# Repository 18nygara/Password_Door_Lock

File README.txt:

Password based door locking mechanism - 12 key allows user to input a password which will be reflected on the screen provided on the unit. USB interface allows 
one to set a password and change settings in the device, software is not included in the repo.

WARNING! ~~~ IF TRYING TO COPY THIS REPO, IT WILL NOT WORK ON YOUR LOCAL MACHINE ~~~

Because of the absolute pathing on KiCAD file libraries, downloading this project will NOT allow one to modify the design.
All footprint, 3D, and library modules were provided via UltraLibrarian, SnapEDA, DigiKey, or were custom designed - they can be resourced but not copied directly from here.

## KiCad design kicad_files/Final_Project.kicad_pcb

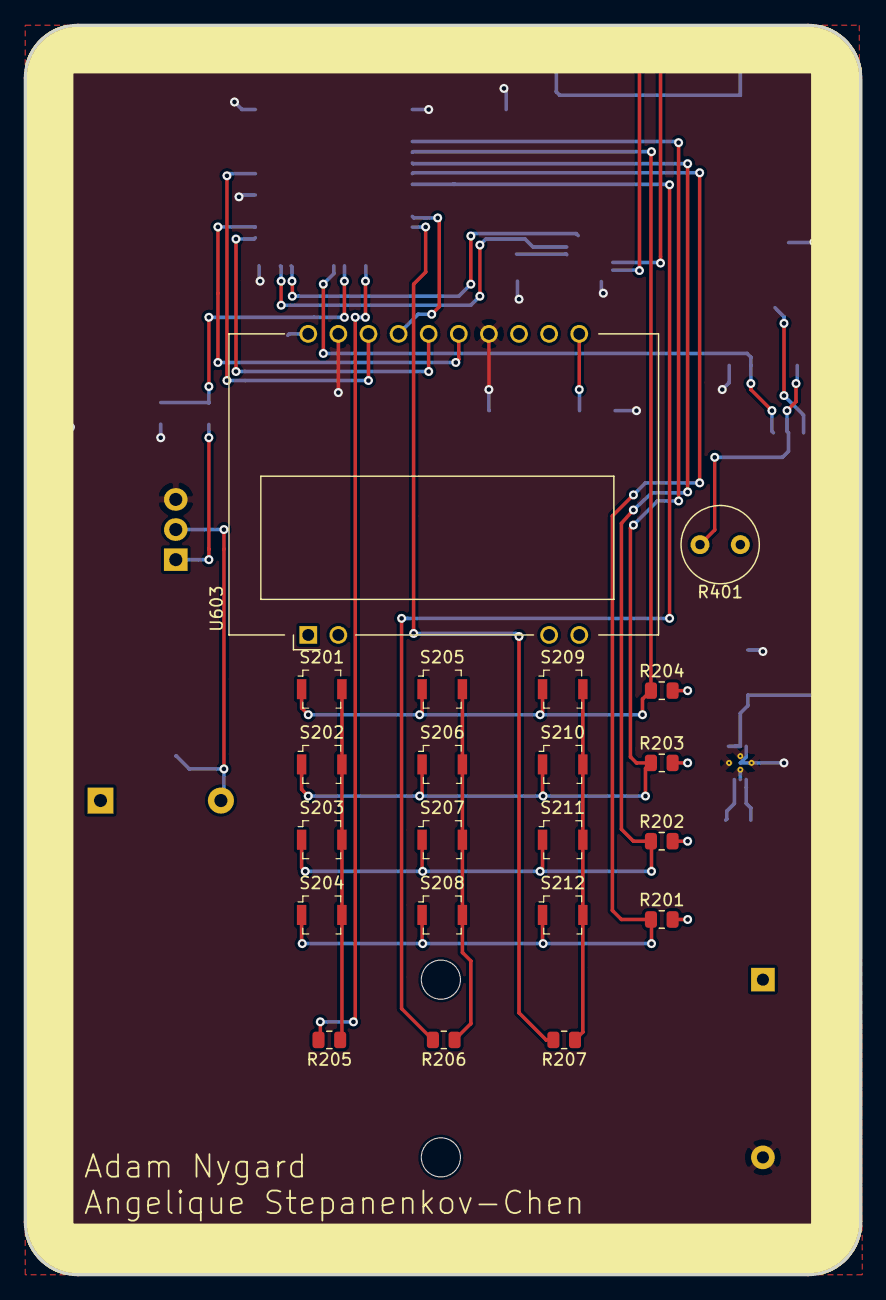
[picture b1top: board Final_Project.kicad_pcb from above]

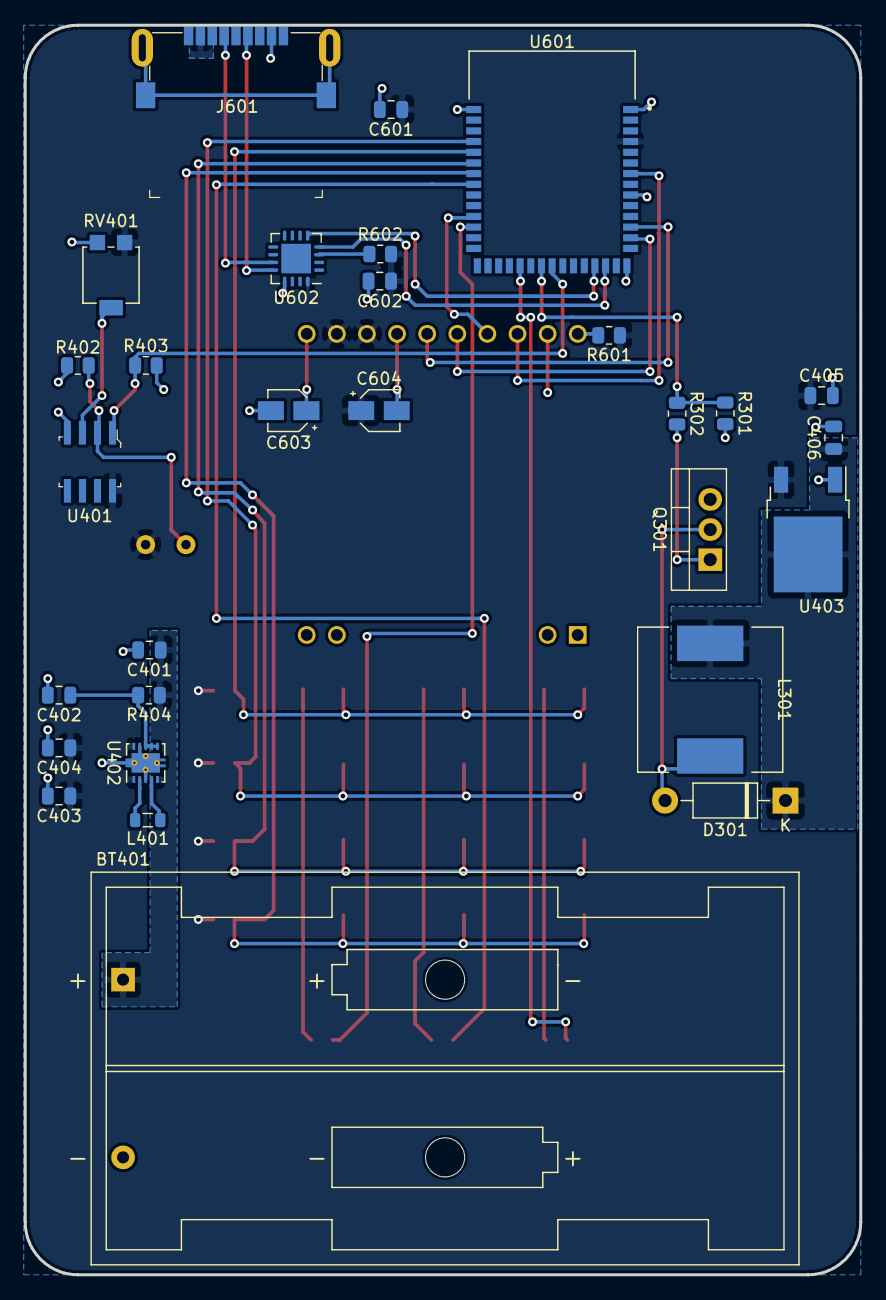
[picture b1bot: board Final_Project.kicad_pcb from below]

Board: 2 copper layers, 70.5 x 105.4 mm, 50 parts (29 on the bottom side), 34 nets.

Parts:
BT401: 3V; BatteryHolder_Keystone_2462_2xAA
C401, C403, C404, C405, C406, C601, C602: 10uF; C_0805_2012Metric
C402: 0.1uF; C_0805_2012Metric
C603, C604: 1uF; CP_Elec_3x5.3
D301: 1N4007; D_DO-41_SOD81_P10.16mm_Horizontal
J601: AU-Y1006-3; USB_A_Female_AU-Y1006-3
L301: 322mH; L_Pulse_PA4320
L401: 2.2uH; L_0805_2012Metric
Q301: IRF540N; TO-220-3_Vertical
R201, R202, R203, R204, R301, R302, R402: 10K; R_0805_2012Metric
R205, R206, R207, R403: 470; R_0805_2012Metric
R401: A1050; R_LDR_D6.4mm_P3.4mm_Vertical
R404: 100; R_0805_2012Metric
R601, R602: 10k; R_0805_2012Metric
RV401: 20K; Potentiometer_Bourns_3314G_Vertical
S201, S202, S203, S204, S205, S206, S207, S208, S209, S210, S211, S212: B3U-1000P; Switch_Tactile_SMD_B3U-1000P
U401: LM358DR; SOIC-8_W3.9mm
U402: TPS63001; Texas_DRC0010J_ThermalVias
U403: NCP1117-12_TO252; TO-252-2
U601: CYBLE-416045-02; XCVR_CYBLE-416045-02
U602: MCP2221AxML; QFN-16-1EP_4x4mm_P0.65mm_EP2.5x2.5mm
U603: EA_DOGS104B-A; EA_DOGS104X-A

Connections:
+3V3: C403.1, C404.1, C405.1, C601.1, C602.1, C604.1, R201.2, R202.2, R203.2, R204.2, R401.1, R601.1, R602.2, RV401.1, U401.8, U402.1, U402.10, U403.3, U601.4, U602.16, U603.12, U603.13
+12V: C406.1, D301.1, L301.1, U403.2
/Keypad/KYPD_CL_0: R205.2, U601.25
/Keypad/KYPD_CL_1: R206.2, U601.36
/Keypad/KYPD_CL_2: R207.2, U601.32
/Keypad/KYPD_COL_CNCT0: R205.1, S201.2, S202.2, S203.2, S204.2
/Keypad/KYPD_COL_CNCT1: R206.1, S205.2, S206.2, S207.2, S208.2
/Keypad/KYPD_COL_CNCT2: R207.1, S209.2, S210.2, S211.2, S212.2
/Keypad/KYPD_RW_0: R204.1, S201.1, S205.1, S209.1, U601.39
/Keypad/KYPD_RW_1: R203.1, S202.1, S206.1, S210.1, U601.40
/Keypad/KYPD_RW_2: R202.1, S203.1, S207.1, S211.1, U601.38
/Keypad/KYPD_RW_3: R201.1, S204.1, S208.1, S212.1, U601.37
/Light_Sensor/LIGHT_DIV: R401.2, R402.1, U401.2
/Light_Sensor/LIGHT_OUT: R403.1, U401.1, U601.22
/Light_Sensor/V_THRESH: RV401.2, U401.3
/Lock_Mechanism/MOS_GATE: Q301.1, R302.2
/Lock_Mechanism/MTR_CTRL: D301.2, L301.2, Q301.2
/Lock_Mechanism/MTR_ON: R301.1, R302.1, U601.23
/MCU/D+: J601.3, U602.12
/MCU/D-: J601.2, U602.11
/MCU/RST_N_SCR: R601.2, U603.20
/MCU/RST_N_USB: R602.1, U602.3
/MCU/V_OUT_SCR: C603.1, U603.11
/Power_Supply/EN: C402.1, R404.2, U402.6, U402.7, U402.8
/Power_Supply/INDCTR_LFT: L401.1, U402.4
/Power_Supply/INDCTR_RGHT: L401.2, U402.2
/Power_Supply/VBAT_IN: BT401.1, C401.1, R404.1, U402.5
GND: BT401.2, C401.2, C402.2, C403.2, C404.2, C405.2, C406.2, C601.2, C602.2, C603.2, C604.2, J601.4, Q301.3, R301.2, R402.2, R403.2, RV401.3, U401.4, U402.3, U402.9, U402.11, U403.1, U601.1, U601.9, U601.15, U601.43, U602.13, U603.14, U603.19
MISO: U601.12, U603.15
MOSI: U601.13, U603.16
SCLK: U601.33, U603.17
SS_0: U601.7, U603.18
USB_UART_RX: U601.17, U602.4
USB_UART_TX: U601.18, U602.5

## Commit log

2021-04-30 Add initial KiCAD files
2021-04-30 Add PCB and 3D rendering images of the final product
2021-04-30 Add README file for pathing warnings
2021-09-01 Fixed Spelling mistake
